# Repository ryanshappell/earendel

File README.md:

# earendel
A modular ringlight for microscopes

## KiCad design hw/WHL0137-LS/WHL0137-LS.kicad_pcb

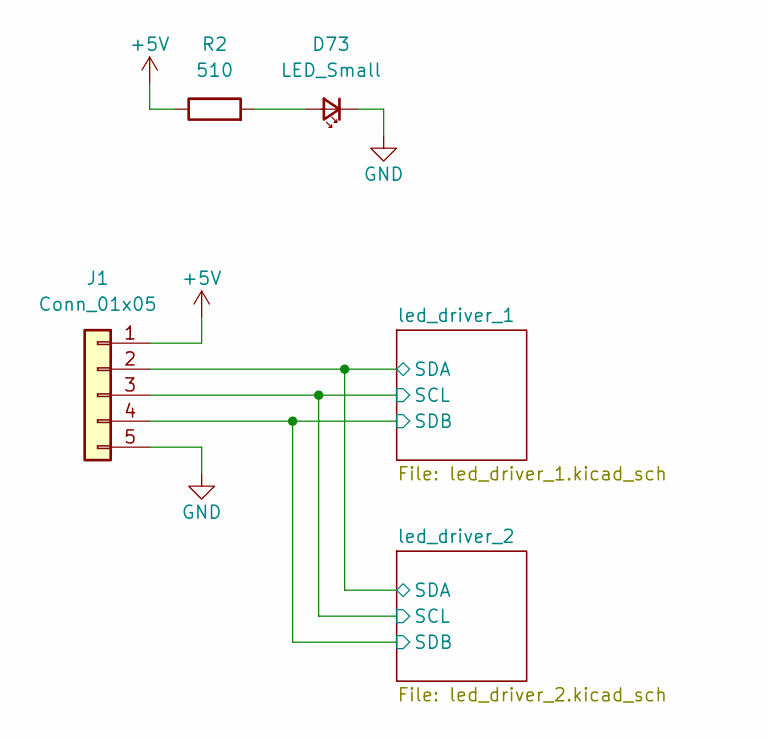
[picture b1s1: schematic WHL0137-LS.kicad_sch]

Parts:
D73: LED_Small; LED_0805_2012Metric
J1: Conn_01x05; JST_EH_S5B-EH_1x05_P2.50mm_Horizontal
R2: 510; R_0805_2012Metric

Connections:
+5V: J1.1, R2.1; also elsewhere on the board
/led_driver_1/SCL: J1.3; also elsewhere on the board
/led_driver_1/SDA: J1.2; also elsewhere on the board
/led_driver_1/SDB: J1.4; also elsewhere on the board
GND: D73.1 (K), J1.5; also elsewhere on the board
unnamed: D73.2 (A), R2.2

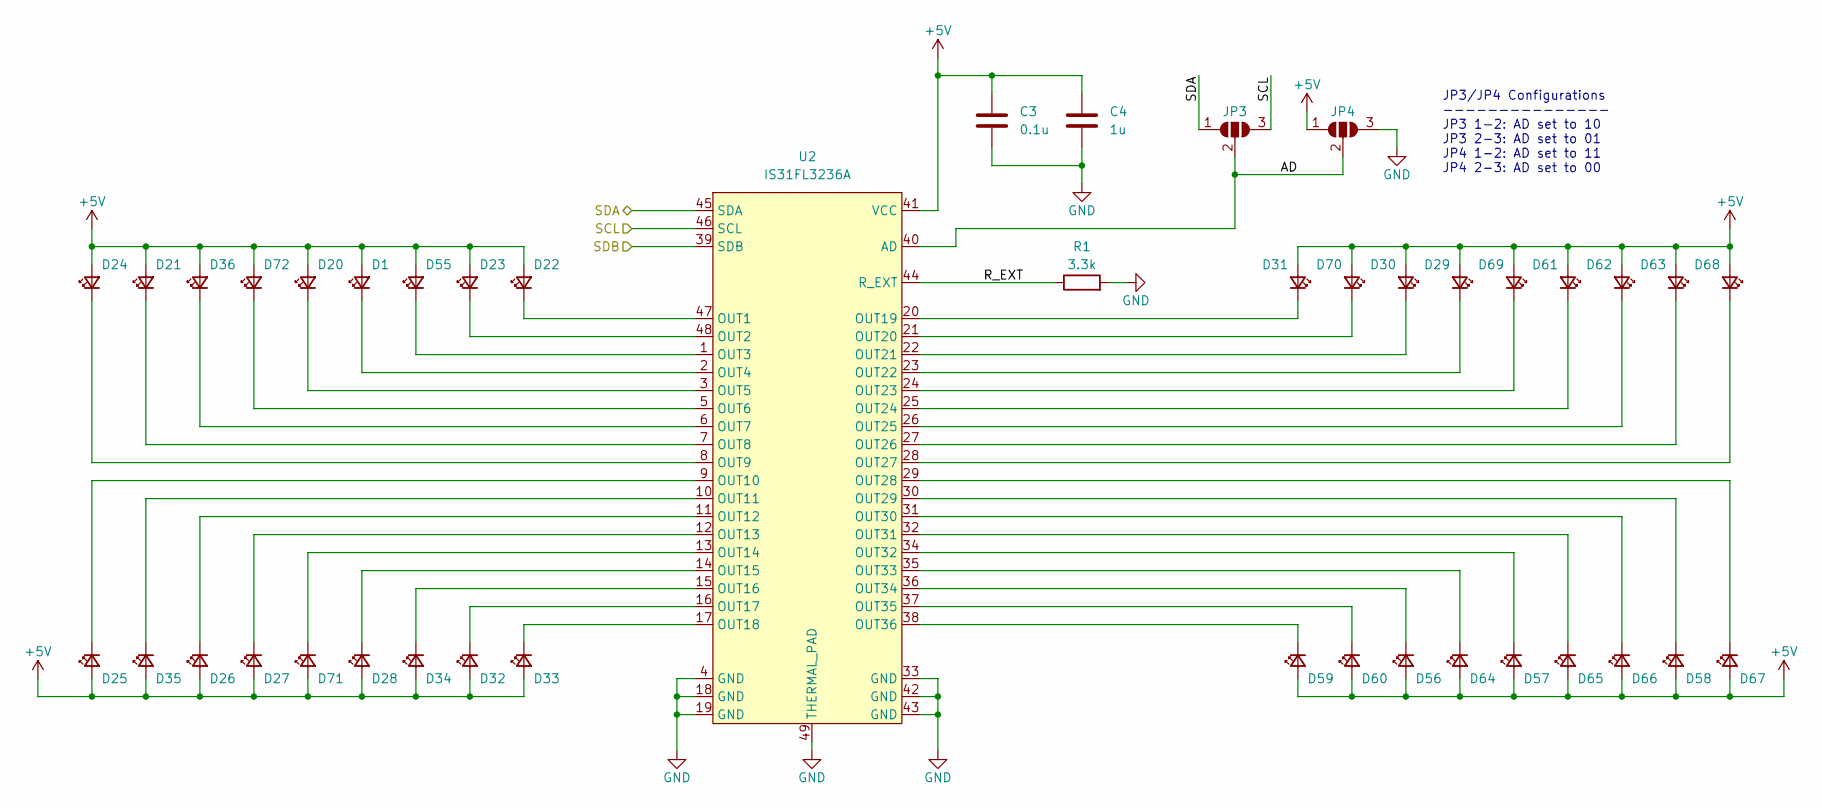
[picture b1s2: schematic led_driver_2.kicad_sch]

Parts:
C3: 0.1u; C_0805_2012Metric
C4: 1u; C_0805_2012Metric
D1, D20, D21, D22, D23, D24, D25, D26, D27, D28, D29, D30, D31, D32, D33, D34, D35, D36, D55, D56, D57, D58, D59, D60, D61, D62, D63, D64, D65, D66, D67, D68, D69, D70, D71, D72: LED_Small; LED_D5.0mm
JP3, JP4: SolderJumper_3_Open; SolderJumper-3_P2.0mm_Open_TrianglePad1.0x1.5mm_NumberLabels
R1: 3.3k; R_0805_2012Metric
U2: IS31FL3236A; TQFP-48-1EP_7x7mm_P0.5mm_EP5x5mm_ThermalVias

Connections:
+5V: C3.1, C4.1, D1.2 (A), D20.2 (A), D21.2 (A), D22.2 (A), D23.2 (A), D24.2 (A), D25.2 (A), D26.2 (A), D27.2 (A), D28.2 (A), D29.2 (A), D30.2 (A), D31.2 (A), D32.2 (A), D33.2 (A), D34.2 (A), D35.2 (A), D36.2 (A), D55.2 (A), D56.2 (A), D57.2 (A), D58.2 (A), D59.2 (A), D60.2 (A), D61.2 (A), D62.2 (A), D63.2 (A), D64.2 (A), D65.2 (A), D66.2 (A), D67.2 (A), D68.2 (A), D69.2 (A), D70.2 (A), D71.2 (A), D72.2 (A), JP4.1 (A), U2.41 (VCC); also elsewhere on the board
/led_driver_1/SCL: JP3.3 (B), U2.46 (SCL); also elsewhere on the board
/led_driver_1/SDA: JP3.1 (A), U2.45 (SDA); also elsewhere on the board
/led_driver_1/SDB: U2.39 (SDB); also elsewhere on the board
/led_driver_2/AD: JP3.2 (C), JP4.2 (C), U2.40 (AD)
/led_driver_2/R_EXT: R1.1, U2.44 (R_EXT)
GND: C3.2, C4.2, JP4.3 (B), R1.2, U2.4 (GND), U2.18 (GND), U2.19 (GND), U2.33 (GND), U2.42 (GND), U2.43 (GND), U2.49 (THERMAL_PAD); also elsewhere on the board
unnamed: D1.1 (K), U2.2 (OUT4)
unnamed: D20.1 (K), U2.3 (OUT5)
unnamed: D21.1 (K), U2.7 (OUT8)
unnamed: D22.1 (K), U2.47 (OUT1)
unnamed: D23.1 (K), U2.48 (OUT2)
unnamed: D24.1 (K), U2.8 (OUT9)
unnamed: D25.1 (K), U2.9 (OUT10)
unnamed: D26.1 (K), U2.11 (OUT12)
unnamed: D27.1 (K), U2.12 (OUT13)
unnamed: D28.1 (K), U2.14 (OUT15)
unnamed: D29.1 (K), U2.23 (OUT22)
unnamed: D30.1 (K), U2.22 (OUT21)
unnamed: D31.1 (K), U2.20 (OUT19)
unnamed: D32.1 (K), U2.16 (OUT17)
unnamed: D33.1 (K), U2.17 (OUT18)
unnamed: D34.1 (K), U2.15 (OUT16)
unnamed: D35.1 (K), U2.10 (OUT11)
unnamed: D36.1 (K), U2.6 (OUT7)
unnamed: D55.1 (K), U2.1 (OUT3)
unnamed: D56.1 (K), U2.36 (OUT34)
unnamed: D57.1 (K), U2.34 (OUT32)
unnamed: D58.1 (K), U2.30 (OUT29)
unnamed: D59.1 (K), U2.38 (OUT36)
unnamed: D60.1 (K), U2.37 (OUT35)
unnamed: D61.1 (K), U2.25 (OUT24)
unnamed: D62.1 (K), U2.26 (OUT25)
unnamed: D63.1 (K), U2.27 (OUT26)
unnamed: D64.1 (K), U2.35 (OUT33)
unnamed: D65.1 (K), U2.32 (OUT31)
unnamed: D66.1 (K), U2.31 (OUT30)
unnamed: D67.1 (K), U2.29 (OUT28)
unnamed: D68.1 (K), U2.28 (OUT27)
unnamed: D69.1 (K), U2.24 (OUT23)
unnamed: D70.1 (K), U2.21 (OUT20)
unnamed: D71.1 (K), U2.13 (OUT14)
unnamed: D72.1 (K), U2.5 (OUT6)

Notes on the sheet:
JP3/JP4 Configurations --------------- JP3 1-2: AD set to 10 JP3 2-3: AD set to 01 JP4 1-2: AD set to 11 JP4 2-3: AD set to 00

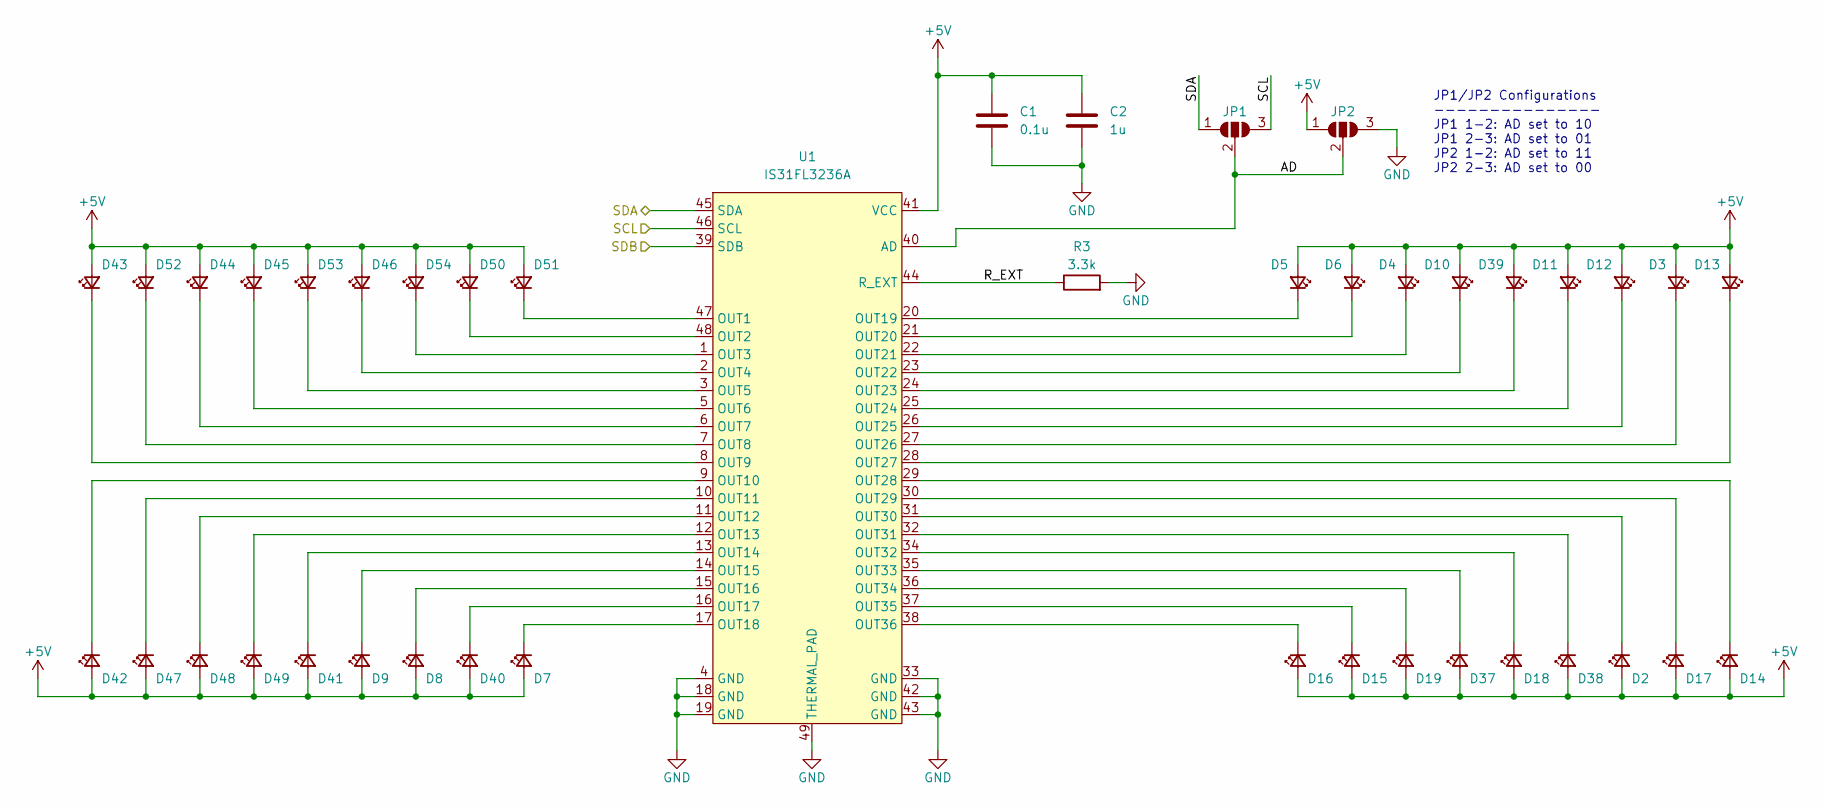
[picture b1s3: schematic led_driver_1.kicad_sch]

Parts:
C1: 0.1u; C_0805_2012Metric
C2: 1u; C_0805_2012Metric
D2, D3, D4, D5, D6, D7, D8, D9, D10, D11, D12, D13, D14, D15, D16, D17, D18, D19, D37, D38, D39, D40, D41, D42, D43, D44, D45, D46, D47, D48, D49, D50, D51, D52, D53, D54: LED_Small; LED_D5.0mm
JP1, JP2: SolderJumper_3_Open; SolderJumper-3_P2.0mm_Open_TrianglePad1.0x1.5mm_NumberLabels
R3: 3.3k; R_0805_2012Metric
U1: IS31FL3236A; TQFP-48-1EP_7x7mm_P0.5mm_EP5x5mm_ThermalVias

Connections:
+5V: C1.1, C2.1, D2.2 (A), D3.2 (A), D4.2 (A), D5.2 (A), D6.2 (A), D7.2 (A), D8.2 (A), D9.2 (A), D10.2 (A), D11.2 (A), D12.2 (A), D13.2 (A), D14.2 (A), D15.2 (A), D16.2 (A), D17.2 (A), D18.2 (A), D19.2 (A), D37.2 (A), D38.2 (A), D39.2 (A), D40.2 (A), D41.2 (A), D42.2 (A), D43.2 (A), D44.2 (A), D45.2 (A), D46.2 (A), D47.2 (A), D48.2 (A), D49.2 (A), D50.2 (A), D51.2 (A), D52.2 (A), D53.2 (A), D54.2 (A), JP2.1 (A), U1.41 (VCC); also elsewhere on the board
/led_driver_1/AD: JP1.2 (C), JP2.2 (C), U1.40 (AD)
/led_driver_1/R_EXT: R3.1, U1.44 (R_EXT)
/led_driver_1/SCL: JP1.3 (B), U1.46 (SCL); also elsewhere on the board
/led_driver_1/SDA: JP1.1 (A), U1.45 (SDA); also elsewhere on the board
/led_driver_1/SDB: U1.39 (SDB); also elsewhere on the board
GND: C1.2, C2.2, JP2.3 (B), R3.2, U1.4 (GND), U1.18 (GND), U1.19 (GND), U1.33 (GND), U1.42 (GND), U1.43 (GND), U1.49 (THERMAL_PAD); also elsewhere on the board
unnamed: D2.1 (K), U1.31 (OUT30)
unnamed: D3.1 (K), U1.27 (OUT26)
unnamed: D4.1 (K), U1.22 (OUT21)
unnamed: D5.1 (K), U1.20 (OUT19)
unnamed: D6.1 (K), U1.21 (OUT20)
unnamed: D7.1 (K), U1.17 (OUT18)
unnamed: D8.1 (K), U1.15 (OUT16)
unnamed: D9.1 (K), U1.14 (OUT15)
unnamed: D10.1 (K), U1.23 (OUT22)
unnamed: D11.1 (K), U1.25 (OUT24)
unnamed: D12.1 (K), U1.26 (OUT25)
unnamed: D13.1 (K), U1.28 (OUT27)
unnamed: D14.1 (K), U1.29 (OUT28)
unnamed: D15.1 (K), U1.37 (OUT35)
unnamed: D16.1 (K), U1.38 (OUT36)
unnamed: D17.1 (K), U1.30 (OUT29)
unnamed: D18.1 (K), U1.34 (OUT32)
unnamed: D19.1 (K), U1.36 (OUT34)
unnamed: D37.1 (K), U1.35 (OUT33)
unnamed: D38.1 (K), U1.32 (OUT31)
unnamed: D39.1 (K), U1.24 (OUT23)
unnamed: D40.1 (K), U1.16 (OUT17)
unnamed: D41.1 (K), U1.13 (OUT14)
unnamed: D42.1 (K), U1.9 (OUT10)
unnamed: D43.1 (K), U1.8 (OUT9)
unnamed: D44.1 (K), U1.6 (OUT7)
unnamed: D45.1 (K), U1.5 (OUT6)
unnamed: D46.1 (K), U1.2 (OUT4)
unnamed: D47.1 (K), U1.10 (OUT11)
unnamed: D48.1 (K), U1.11 (OUT12)
unnamed: D49.1 (K), U1.12 (OUT13)
unnamed: D50.1 (K), U1.48 (OUT2)
unnamed: D51.1 (K), U1.47 (OUT1)
unnamed: D52.1 (K), U1.7 (OUT8)
unnamed: D53.1 (K), U1.3 (OUT5)
unnamed: D54.1 (K), U1.1 (OUT3)

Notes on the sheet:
JP1/JP2 Configurations --------------- JP1 1-2: AD set to 10 JP1 2-3: AD set to 01 JP2 1-2: AD set to 11 JP2 2-3: AD set to 00

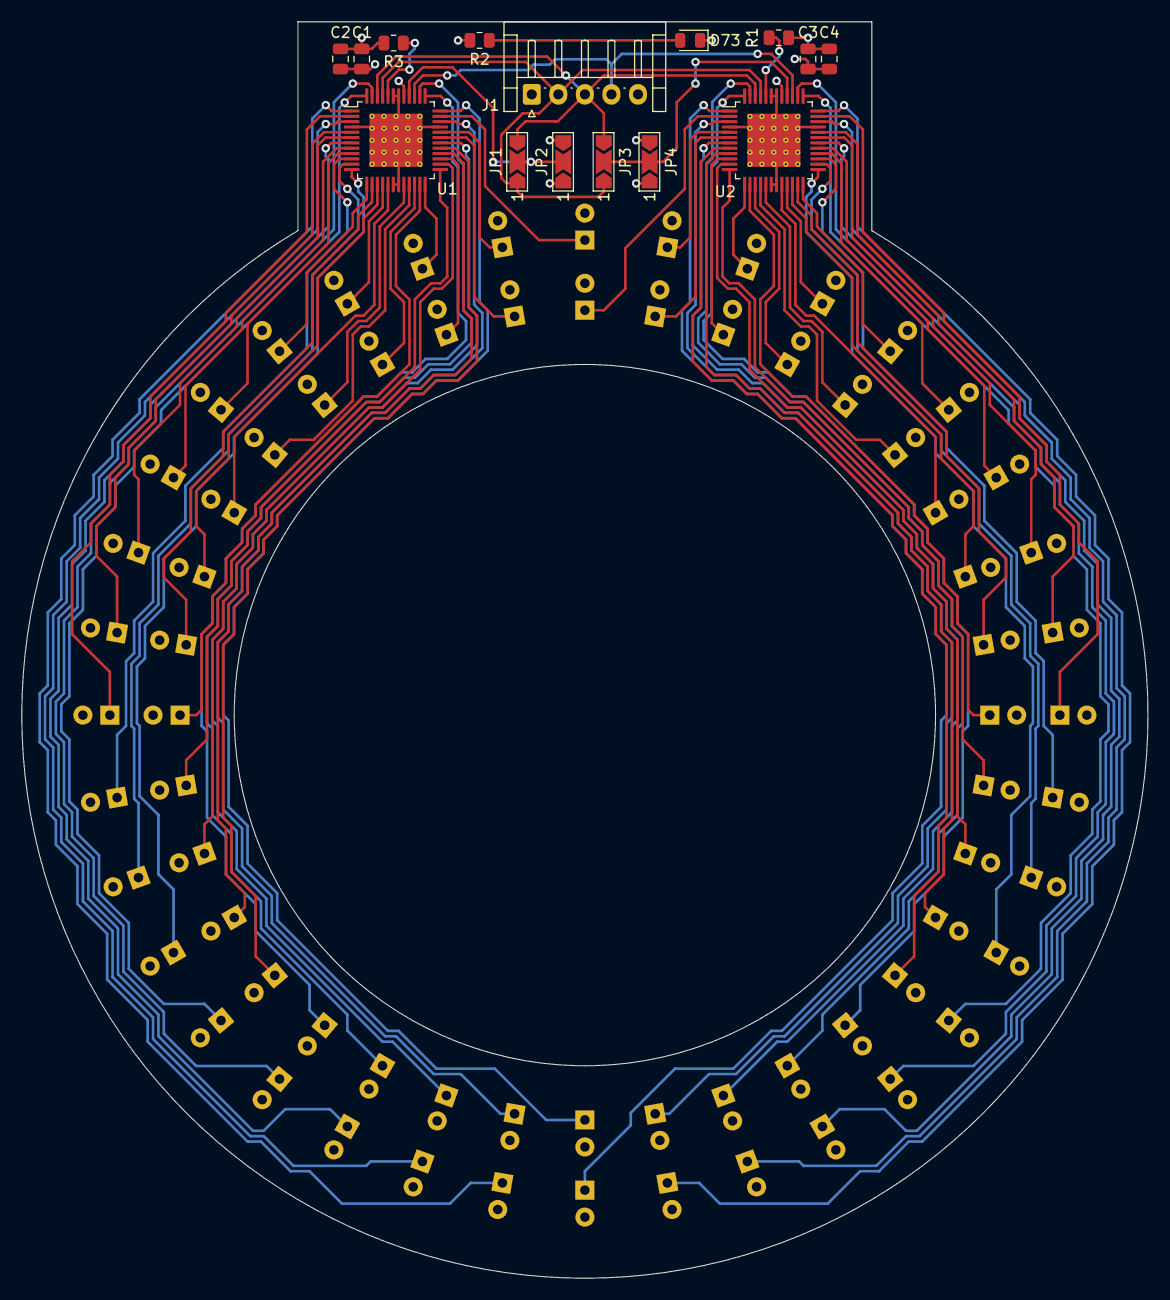
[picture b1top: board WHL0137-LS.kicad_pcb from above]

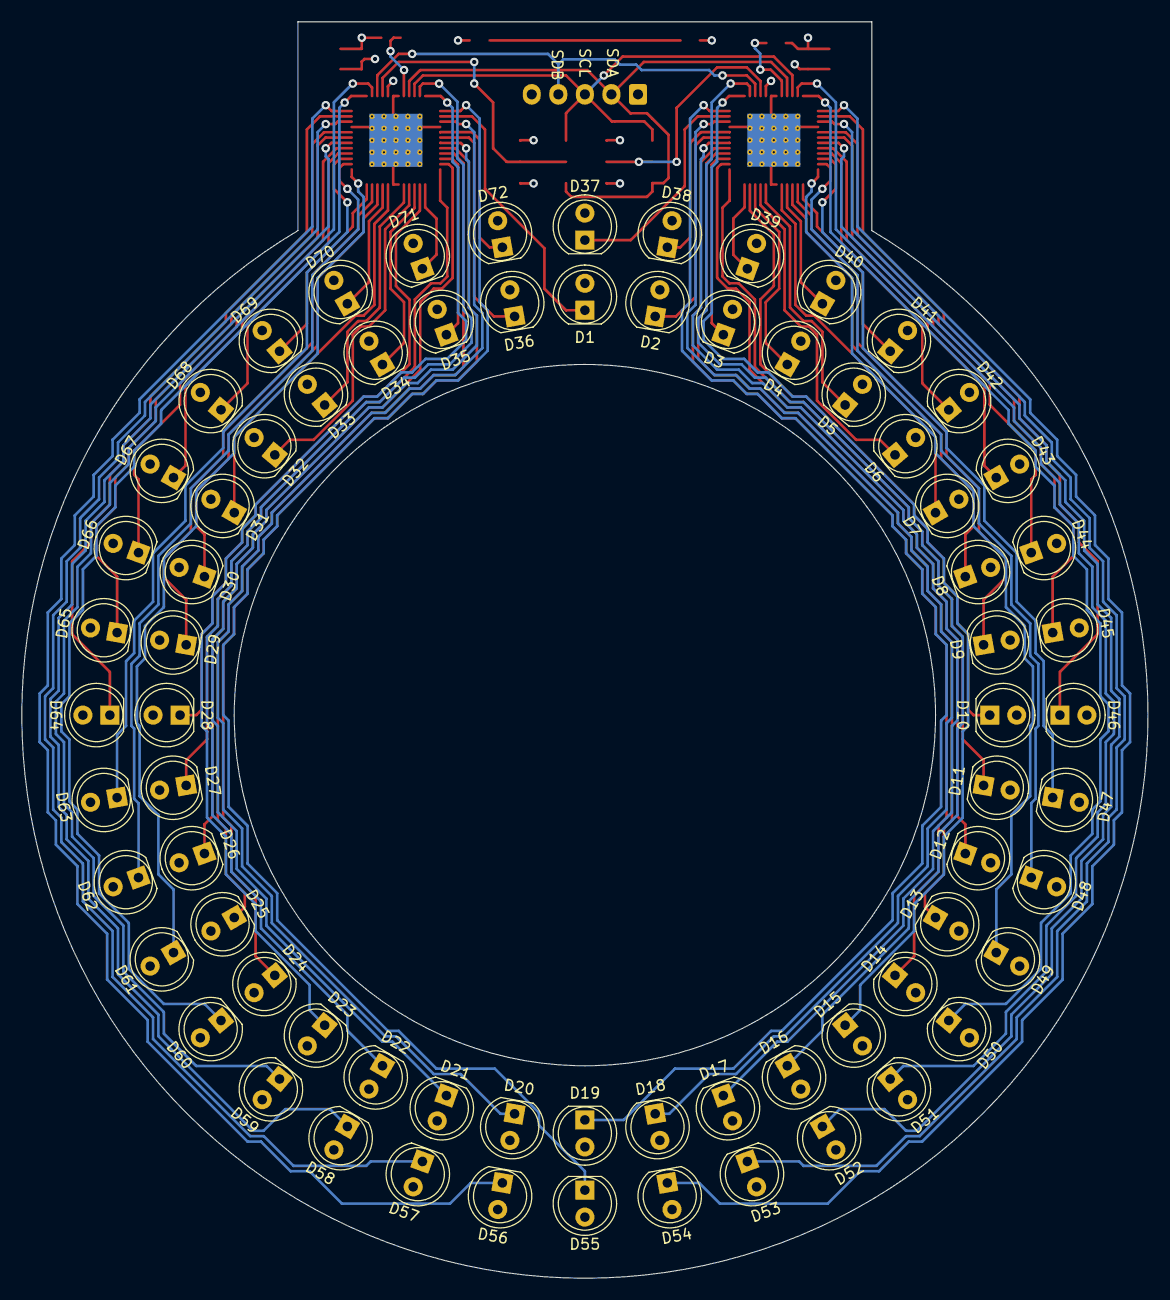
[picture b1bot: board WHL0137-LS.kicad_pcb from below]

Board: 4 copper layers, 106.0 x 118.2 mm, 87 parts (72 on the bottom side), 82 nets.

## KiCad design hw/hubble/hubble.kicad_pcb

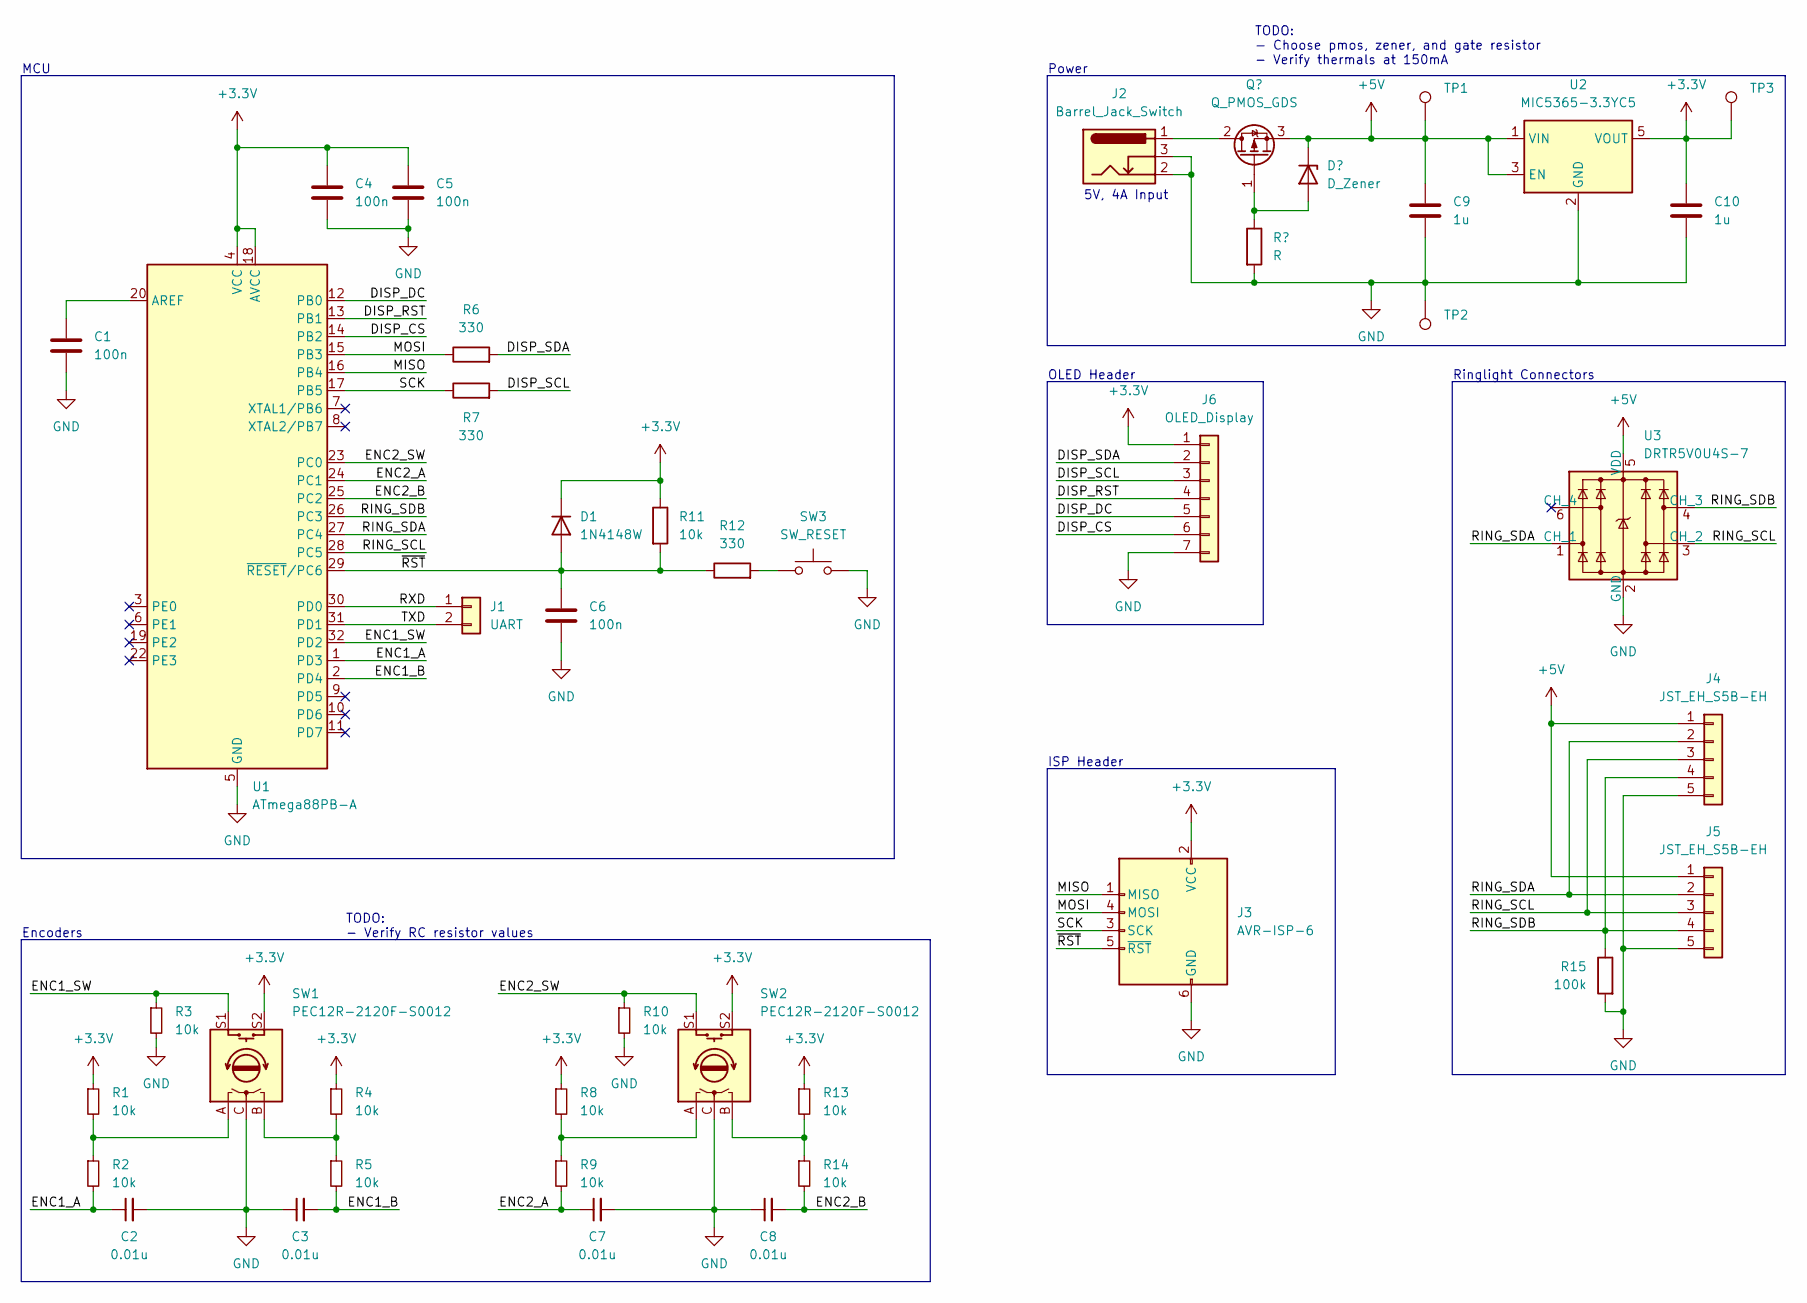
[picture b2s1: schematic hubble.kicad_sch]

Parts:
C1, C4, C5, C6: 100n; C_0805_2012Metric
C2, C3, C7, C8: 0.01u; C_0805_2012Metric
C9, C10: 1u; C_0805_2012Metric
D1: 1N4148W; D_SOD-123
J1: UART; PinHeader_1x02_P2.54mm_Vertical
J2: Barrel_Jack_Switch; BarrelJack_Horizontal
J3: AVR-ISP-6; PinHeader_2x03_P2.54mm_Vertical
J4, J5: JST_EH_S5B-EH; JST_EH_S5B-EH_1x05_P2.50mm_Horizontal
J6: OLED_Display; PinHeader_1x07_P2.54mm_Vertical
R1, R2, R3, R4, R5, R8, R9, R10, R11, R13, R14: 10k; R_0805_2012Metric
R6, R7, R12: 330; R_0805_2012Metric
R15: 100k; R_0805_2012Metric
SW1, SW2: PEC12R-2120F-S0012
SW3: SW_RESET; SW_PUSH_6mm
TP1, TP2, TP3: TestPoint; TestPoint_THTPad_D2.0mm_Drill1.0mm
U1: ATmega88PB-A; TQFP-32_7x7mm_P0.8mm
U2: MIC5365-3.3YC5; SOT-353_SC-70-5
U3: DRTR5V0U4S-7; SOT-363_SC-70-6

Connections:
+3.3V: C4.1, C5.1, C10.1, D1.1 (K), J3.2 (VCC), J6.1, R1.1, R4.1, R8.1, R11.1, R13.1, SW1.S2, SW2.S2, TP3.1, U1.4 (VCC), U1.18 (AVCC), U2.5 (VOUT)
+5V: C9.1, J2.1, J4.1, J5.1, TP1.1, U2.1 (VIN), U2.3 (EN), U3.5 (VDD)
/DISP_CS: J6.6, U1.14 (PB2)
/DISP_DC: J6.5, U1.12 (PB0)
/DISP_RST: J6.4, U1.13 (PB1)
/DISP_SCL: J6.3, R7.2
/DISP_SDA: J6.2, R6.2
/ENC1_A: C2.1, R2.2, U1.1 (PD3)
/ENC1_B: C3.2, R5.2, U1.2 (PD4)
/ENC1_SW: R3.1, SW1.S1, U1.32 (PD2)
/ENC2_A: C7.1, R9.2, U1.24 (PC1)
/ENC2_B: C8.2, R14.2, U1.25 (PC2)
/ENC2_SW: R10.1, SW2.S1, U1.23 (PC0)
/MISO: J3.1 (MISO), U1.16 (PB4)
/MOSI: J3.4 (MOSI), R6.1, U1.15 (PB3)
/RING_SCL: J4.3, J5.3, U1.28 (PC5), U3.3 (CH_2)
/RING_SDA: J4.2, J5.2, U1.27 (PC4), U3.1 (CH_1)
/RING_SDB: J4.4, J5.4, R15.1, U1.26 (PC3), U3.4 (CH_3)
/RXD: J1.1, U1.30 (PD0)
/SCK: J3.3 (SCK), R7.1, U1.17 (PB5)
/TXD: J1.2, U1.31 (PD1)
/~RST: C6.1, D1.2 (A), J3.5 (~RST), R11.2, R12.1, U1.29 (~RESET/PC6)
GND: C1.2, C2.2, C3.1, C4.2, C5.2, C6.2, C7.2, C8.1, C9.2, C10.2, J2.2, J2.3, J3.6 (GND), J4.5, J5.5, J6.7, R3.2, R10.2, R15.2, SW1.C, SW2.C, SW3.2, TP2.1, U1.5 (GND), U1.21 (GND), U2.2 (GND), U3.2 (GND)
unnamed: C1.1, U1.20 (AREF)
unnamed: R1.2, R2.1, SW1.A
unnamed: R4.2, R5.1, SW1.B
unnamed: R8.2, R9.1, SW2.A
unnamed: R12.2, SW3.1
unnamed: R13.2, R14.1, SW2.B

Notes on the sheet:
Encoders
OLED Header
ISP Header
TODO: - Verify RC resistor values
5V, 4A Input
Power
TODO: - Choose pmos, zener, and gate resistor - Verify thermals at 150mA
Ringlight Connectors
MCU

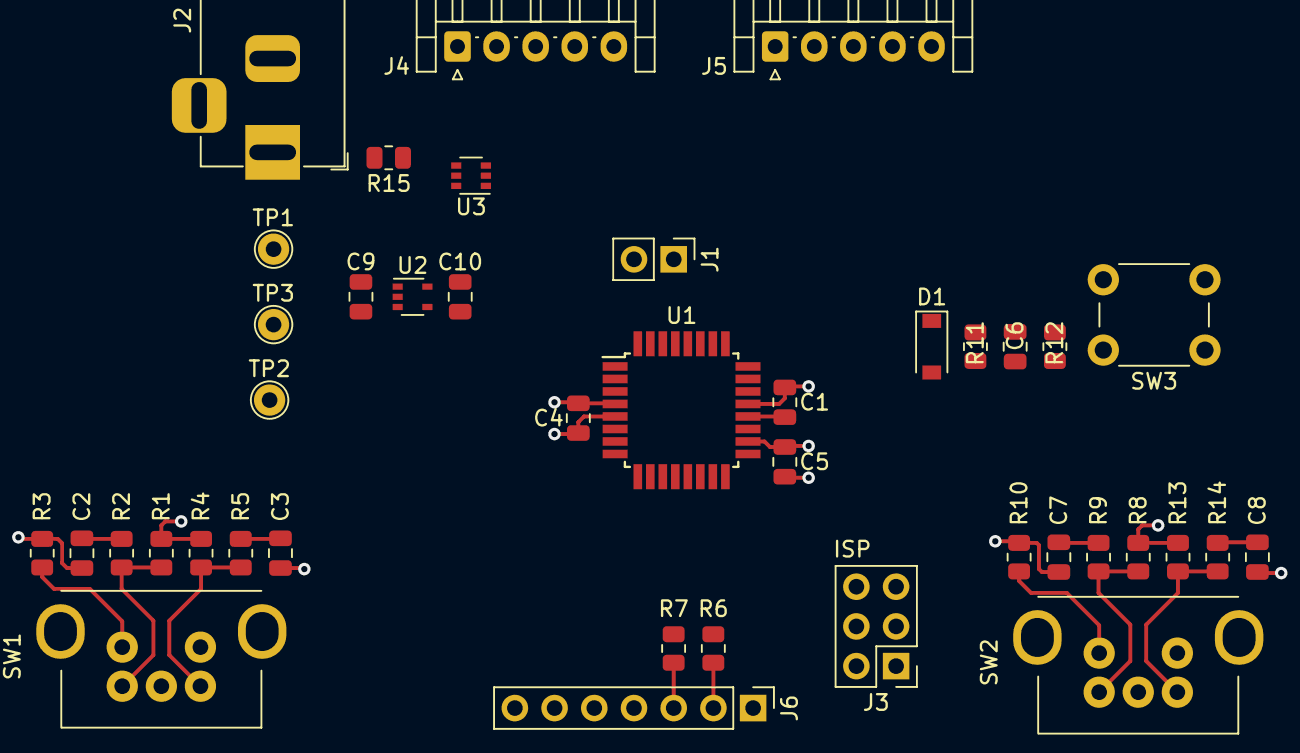
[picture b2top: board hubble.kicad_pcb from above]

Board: 4 copper layers, 41 parts (0 on the bottom side), 29 nets.

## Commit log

2022-07-28 Added base kicad project
2022-07-28 Star discovered
2022-07-28 Initial schematic
2022-07-29 Some floor planning
2022-08-05 Some layout
2022-08-22 Routed LED traces and fixed designators
2022-08-22 Add initial hubble mcu and encoders
2022-08-22 Switch to dc barrel jack, add some todos
2022-08-24 Add 3.3V LDO
2022-08-24 More layout progress
2022-08-27 Start initial hubble layout
2022-08-28 Add reverse polarity protection, more layout
2022-10-01 misc changes
2024-08-30 Purge and start new project in kicad 8
2024-08-30 Add LED ring drivers
2024-08-31 Added MCU decoupling caps, started power
